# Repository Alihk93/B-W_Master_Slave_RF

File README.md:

# B-W_Master_Slave_RF
Design, validate, and release two manufacturable PCBs that together form a one-way wireless link: a solar-powered remote node (**R_Slave**) transmits a 433.92 MHz ASK/OOK signal to a mains-powered base unit (**Master_T**), which relays the received data to a host PC over USB. The end state is a complete KiCad design package — schematic, layout, BOM

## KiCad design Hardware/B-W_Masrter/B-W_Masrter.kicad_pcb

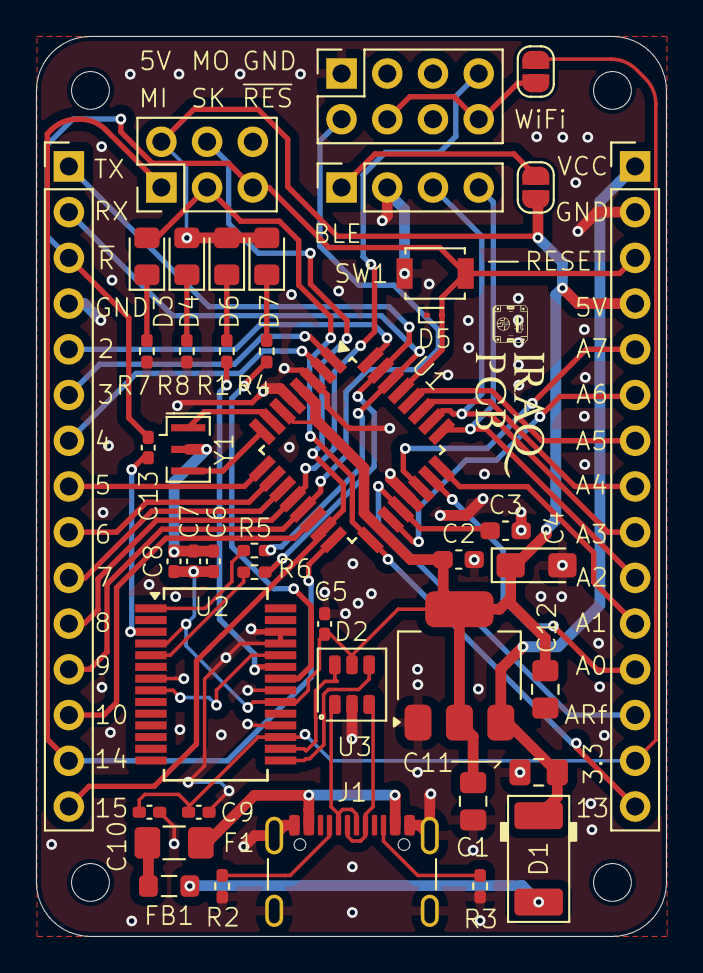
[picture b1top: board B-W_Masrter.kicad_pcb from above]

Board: 2 copper layers, 35.0 x 50.0 mm, 47 parts (0 on the bottom side), 50 nets.

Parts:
C1: 1u; C_0805_2012Metric_Pad1.18x1.45mm_HandSolder
C2, C3: 100n; C_0603_1608Metric_Pad1.08x0.95mm_HandSolder
C4: 4u7/16V; CP_EIA-3216-12_Kemet-S_Pad1.58x1.35mm_HandSolder
C5, C8, C9, C13: 100n; C_0402_1005Metric_Pad0.74x0.62mm_HandSolder
C6: 22u; C_0402_1005Metric_Pad0.74x0.62mm_HandSolder
C7, C10: 4u7; C_0402_1005Metric_Pad0.74x0.62mm_HandSolder
C11, C12: 22u; C_0805_2012Metric_Pad1.18x1.45mm_HandSolder
D1: 1N5817M; D_MELF
D2: USBLC6-2SC6; SOT-23-6
D3: Yallow; LED_0805_2012Metric_Pad1.15x1.40mm_HandSolder
D4, D7: Green; LED_0805_2012Metric_Pad1.15x1.40mm_HandSolder
D5: ESD9B3.3ST5G; D_SOD-923
D6: Red; LED_0805_2012Metric_Pad1.15x1.40mm_HandSolder
F1: Polyfuse_1A; Fuse_1206_3216Metric_Pad1.42x1.75mm_HandSolder
FB1: BLM21PG220; L_0805_2012Metric_Pad1.05x1.20mm_HandSolder
H1, H2, H3, H4: MountingHole; MountingHole_2.1mm
J1: USB_C_Receptacle_USB2.0_16P; USB_C_Receptacle_GCT_USB4105-xx-A_16P_TopMnt_Horizontal
J2: Right_Rail; PinHeader_1x15_P2.54mm_Vertical
J3: Left_Rail; PinHeader_1x15_P2.54mm_Vertical
J4: ICSP; PinHeader_2x03_P2.54mm_Vertical
J5: HM10; PinSocket_1x04_P2.54mm_Vertical
J6: ESP8266; PinSocket_2x04_P2.54mm_Vertical
JP1: BLE; SolderJumper-2_P1.3mm_Open_RoundedPad1.0x1.5mm
JP2: WiFi; SolderJumper-2_P1.3mm_Open_RoundedPad1.0x1.5mm
R1, R4, R5, R6, R8: 1K; R_0402_1005Metric_Pad0.72x0.64mm_HandSolder
R2, R3: 5K1; R_0402_1005Metric_Pad0.72x0.64mm_HandSolder
R7: 330R; R_0402_1005Metric_Pad0.72x0.64mm_HandSolder
SW1: BOOT; SW_SPST_B3U-1000P
U1: ATmega328P-A; TQFP-32_7x7mm_P0.8mm
U2: FT232RL; SSOP-28_5.3x10.2mm_P0.65mm
U3: LM1117MP-5.0; SOT-223-3_TabPin2
Y1: 16MHz; Resonator_SMD_Murata_CSTxExxV-3Pin_3.0x1.1mm

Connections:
+3V3: C9.1, C10.1, J3.14, JP2.1 (A), U2.17 (3V3OUT)
+5V: C1.1, C2.1, C4.1, C5.1, C6.1, C7.1, C8.1, C12.1, D2.5 (VP), D4.2 (A), D6.2 (A), D7.2 (A), J3.4, J4.2, JP1.1 (A), U1.4 (VCC), U1.6 (VCC), U1.18 (AVCC), U2.4 (VCCIO), U2.20 (VCC), U3.2 (VO)
/A0: J3.12, U1.23 (PC0)
/A1: J3.11, U1.24 (PC1)
/A2: J3.10, J5.4, U1.25 (PC2)
/A3: J3.9, J5.3, U1.26 (PC3)
/A4: J3.8, U1.27 (PC4)
/A5: J3.7, U1.28 (PC5)
/A6: J3.6, U1.19 (ADC6)
/A7: J3.5, U1.22 (ADC7)
/AREF: C3.1, J3.13, U1.20 (AREF)
/CBUS0: R1.1, U2.23 (CBUS0)
/CBUS1: R4.1, U2.22 (CBUS1)
/CC1: J1.A5 (CC1), R2.1
/CC2: J1.B5 (CC2), R3.1
/D2: J2.5, U1.32 (PD2)
/D3: J2.6, U1.1 (PD3)
/D4: J2.7, U1.2 (PD4)
/D5: J2.8, U1.9 (PD5)
/D6: J2.9, U1.10 (PD6)
/D7: J2.10, U1.11 (PD7)
/D8: J2.11, J6.7, U1.12 (PB0)
/D9: J2.12, J6.2, U1.13 (PB1)
/D10: J2.13, U1.14 (PB2)
/D11/MOSI: J2.15, J4.4, U1.15 (PB3)
/D12/MISO: J2.14, J4.1, U1.16 (PB4)
/D13/SCK: D3.2 (A), J3.15, J4.3, U1.17 (PB5)
/D+: D2.3 (L2), J1.A6 (D+), J1.B6 (D+)
/D-: D2.1 (L1), J1.A7 (D-), J1.B7 (D-)
/RTS: C13.1, U2.3 (RTS)
/RXD: R6.1, U2.5 (RXD)
/RXD0: J2.2, R5.2, U1.30 (PD0)
/TXD: R5.1, U2.1 (TXD)
/TXD0: J2.1, R6.2, U1.31 (PD1)
/USB_D+: D2.4 (L2), U2.15 (USBD+)
/USB_D-: D2.6 (L1), U2.16 (USBD-)
/XTAL1: U1.7 (XTAL1/PB6), Y1.1
/XTAL2: U1.8 (XTAL2/PB7), Y1.3
/~RESET: C13.2, D5.2 (A2), J2.3, J3.3, J4.5, SW1.2, U1.29 (~RESET/PC6)
GND: C1.2, C2.2, C3.2, C4.2, C5.2, C6.2, C7.2, C8.2, C9.2, C10.2, C11.2, C12.2, D2.2 (VN), D5.1 (A1), J1.A1 (GND), J1.A12 (GND), J1.B1 (GND), J1.B12 (GND), J1.S1 (SHIELD), J2.4, J3.2, J4.6, J5.2, J6.1, R2.2, R3.2, R7.1, R8.1, SW1.1, U1.3 (GND), U1.5 (GND), U1.21 (GND), U2.7 (GND), U2.18 (GND), U2.21 (GND), U2.25 (AGND), U2.26 (TEST), U3.1 (GND), Y1.2
unnamed: D1.2 (A), FB1.2
unnamed: D3.1 (K), R7.2
unnamed: D4.1 (K), R8.2
unnamed: D6.1 (K), R1.2
unnamed: D7.1 (K), R4.2
unnamed: F1.2, FB1.1
unnamed: J5.1, JP1.2 (B)
unnamed: J6.4, J6.8, JP2.2 (B)
VBUS: F1.1, J1.A4 (VBUS), J1.A9 (VBUS), J1.B4 (VBUS), J1.B9 (VBUS)
VCC: C11.1, D1.1 (K), J3.1, U3.3 (VI)

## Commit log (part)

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2026-06-30 initialization
